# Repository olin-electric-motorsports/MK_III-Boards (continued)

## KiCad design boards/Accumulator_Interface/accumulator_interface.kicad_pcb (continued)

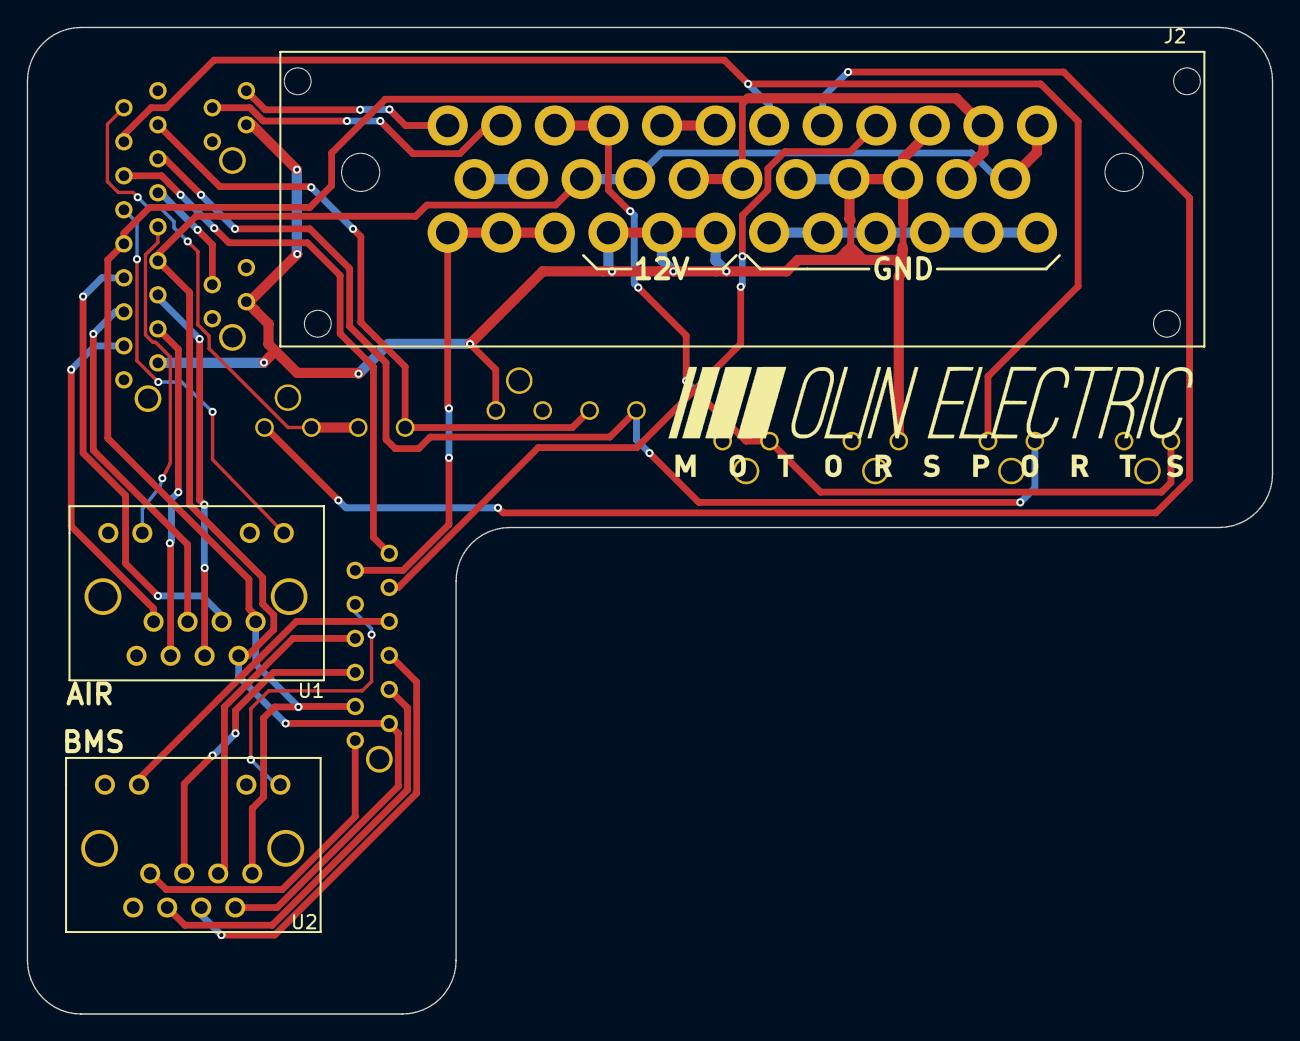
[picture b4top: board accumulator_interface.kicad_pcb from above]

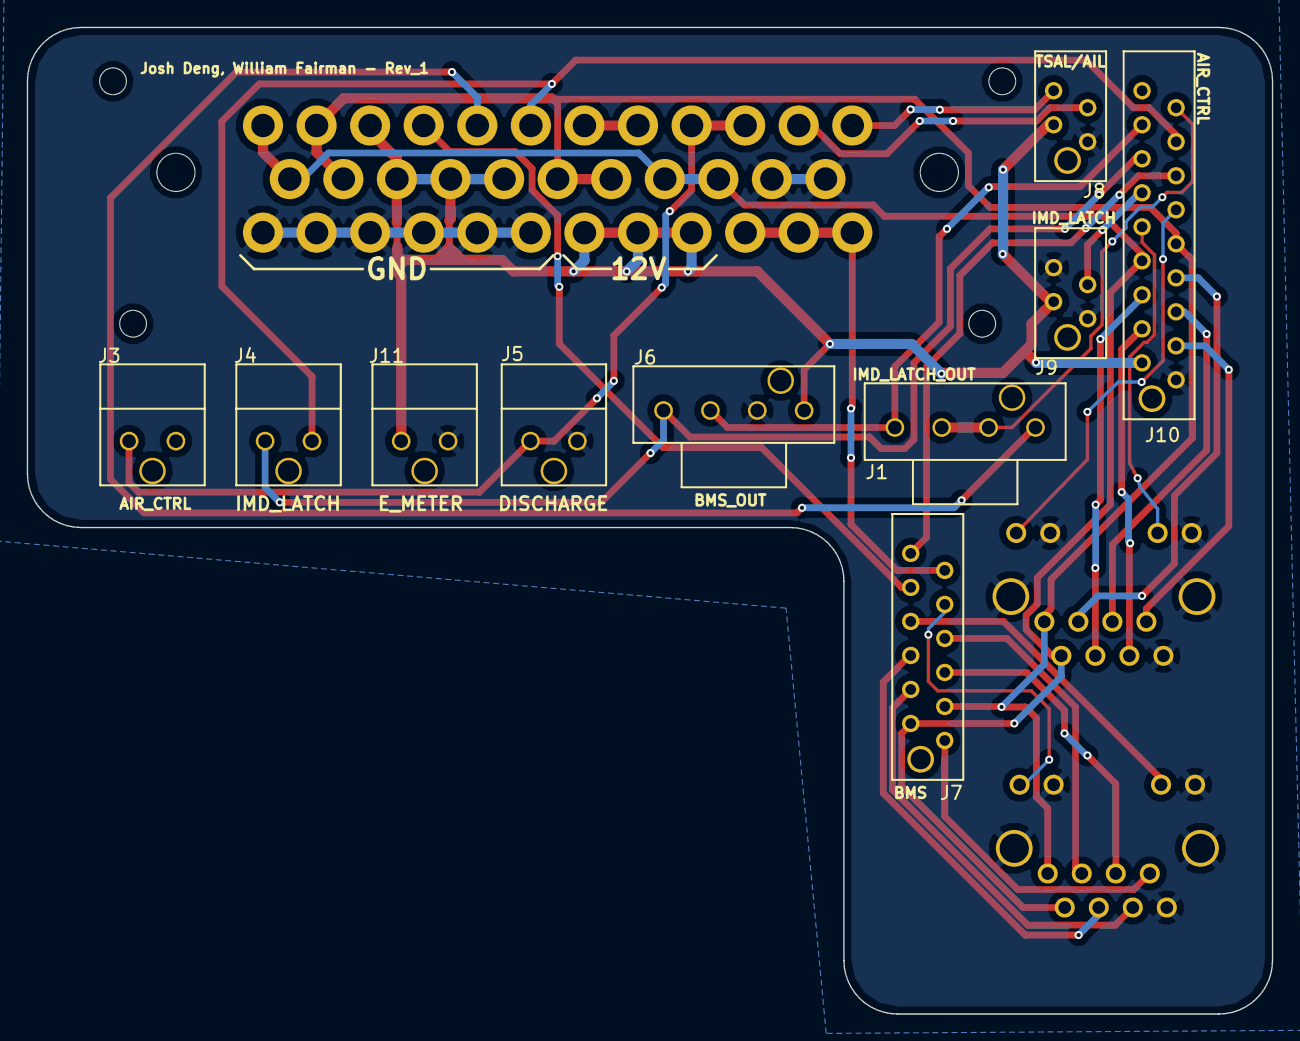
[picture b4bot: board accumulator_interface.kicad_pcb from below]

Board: 2 copper layers, 93.0 x 73.7 mm, 13 parts (10 on the bottom side), 31 nets.

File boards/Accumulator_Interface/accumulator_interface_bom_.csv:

Component,Description,Part,References,Value,Footprint,Quantity Per PCB,Datasheet,Package,MPN,MFN,PurchasingLink,PurchasingLink2,MPN2
1,ULTRAFIT CONN HDR 02CKT,Ultrafit_2,J3,AIR_CTRL,Ultrafit_2,1,,Value,WM11570-ND,Digi-Key,https://www.digikey.com/product-detail/en/molex-llc/17228611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,,
2,CONN FMALE-ON-BRD 18POS VERT T/H,micromatch_female_TOP_ENTRY_locking_18,J10,AIR_CTRL_18,micromatch_female_vert_18,1,,Value,A99500CT-ND,Digi-Key,https://www.digikey.com/product-detail/en/te-connectivity-am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,,
3,CONN FMALE-ON-BRD 12POS VERT T/H,micromatch_female_TOP_ENTRY_locking_12,J7,BMS,micromatch_female_vert_12,1,,Value,A99503CT-ND,Digi-Key,https://www.digikey.com/product-detail/en/te-connectivity-am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,,
4,Ultrafit 4 Pin Connector,Ultrafit_4,J6,BMS_Master,Ultrafit_4,1,http://www.literature.molex.com/SQLImages/kelmscott/Molex/PD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,Value,WM11574-ND,Digi-Key,https://www.digikey.com/products/en?keywords=WM11574-ND,https://www.digikey.com/product-detail/en/molex-llc/17225610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,WM11564-ND
5,ULTRAFIT CONN HDR 02CKT,Ultrafit_2,J5,DISCHARGE,Ultrafit_2,1,,Value,WM11570-ND,Digi-Key,https://www.digikey.com/product-detail/en/molex-llc/17228611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,,
6,Waterproof Panel-Mount Connector RA 35-Pin,Ampseal_35,J2,EXTERNAL,Ampseal_35,1,http://www.te.com/commerce/DocumentDelivery/DDEController?Ac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,,,,,,
7,ULTRAFIT CONN HDR 02CKT,Ultrafit_2,J11,Energy_Meter_Power,Ultrafit_2,1,,Value,WM11570-ND,Digi-Key,https://www.digikey.com/product-detail/en/molex-llc/17228611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,,
8,ULTRAFIT CONN HDR 02CKT,Ultrafit_2,J4,IMD_LATCH,Ultrafit_2,1,,Value,WM11570-ND,Digi-Key,https://www.digikey.com/product-detail/en/molex-llc/17228611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,,
9,CONN FMALE-ON-BRD 4POS VERT T/H,micromatch_female_TOP_ENTRY_locking_4,J9,IMD_LATCH,micromatch_female_vert_4,1,http://www.te.com/commerce/DocumentDelivery/DDEController?Ac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,Value,338068-4,Digi-Key,https://www.digikey.com/product-detail/en/te-connectivity-am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,,
10,Ultrafit 4 Pin Connector,Ultrafit_4,J1,INTERNAL,Ultrafit_4,1,http://www.literature.molex.com/SQLImages/kelmscott/Molex/PD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,Value,WM11574-ND,Digi-Key,https://www.digikey.com/products/en?keywords=WM11574-ND,https://www.digikey.com/product-detail/en/molex-llc/17225610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,WM11564-ND
11,CONN FMALE-ON-BRD 4POS VERT T/H,micromatch_female_TOP_ENTRY_locking_4,J8,TSAL/AIL,micromatch_female_vert_4,1,http://www.te.com/commerce/DocumentDelivery/DDEController?Ac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,Value,338068-4,Digi-Key,https://www.digikey.com/product-detail/en/te-connectivity-am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,,
12,CONN MOD JACK 8P8C VERT UNSHLD,RJ45_VT,U1,RJ45_VT_AIR,RJ45-Vertical,1,https://www.amphenolcanada.com/ProductSearch/drawings/AC/MRJ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,,,,,,
13,CONN MOD JACK 8P8C VERT UNSHLD,RJ45_VT,U2,RJ45_VT_BMS,RJ45-Vertical,1,https://www.amphenolcanada.com/ProductSearch/drawings/AC/MRJ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,,,,,,





Component Groups:,13
Component Count:,13
Fitted Components:,13
Number of PCBs:,1
Total components:,13
Schematic Version:,
Schematic Date:,
BoM Date:,Mon 26 Feb 2018 09:31:12 PM EST
Schematic Source:,/home/william/Desktop/Formula/MK_III-Boards/boards/Accumulator_Interface/accumulator_interface.sch
KiCad Version:,Eeschema 4.0.7-e2-6376~58~ubuntu16.04.1

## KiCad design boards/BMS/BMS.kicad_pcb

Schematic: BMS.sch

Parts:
C1: C_22uF; C_1206_OEM; MPN 1276-2725-1-ND
C2, C4, C5, C9, C15: C_0.1uF; C_0805_OEM; MPN 478-3352-1-ND
C3: C_100pF; C_0805_OEM; MPN 399-1122-1-ND
C6: C_47uF; C_0805_OEM; MPN 587-4280-1-ND
C7, C8: C_30pF; C_0805_OEM; MPN 1276-1130-1-ND
C14: C_10uF_16V; C_0805_OEM; MPN 1276-2399-1-ND
D1, D2, D6, D7, D8: LED_0805; LED_0805_OEM; MPN 475-1410-1-ND
D3: D_Schottky_SOD123; D_SOD-123W_OEM; MPN 1727-2394-1-ND
D4: D_Zener_18V; DO-214AA; MPN SMBJ5355B-TPMSCT-ND
F1: F_500mA_16V; Fuse_1210; MPN 507-1786-1-ND
IC1: ATMEGA16M1; TQFP-32_7x7mm_Pitch0.8mm; MPN ATMEGA16M1-AU-ND
J1, J2, J3, J5: Mounting_Hole_4-40; MPN Value
J4: Ultrafit_4; MPN WM11574-ND
J8: Ultrafit_5; UltraFit_5; MPN WM11667-ND
K1: G5Q-1A4-DC5-5V; Relay_SPST_OMRON-G5Q-1A4_OEM; MPN Z3632-ND
L1: L_4.7uH; 4.7uH_Inductor_OEM; MPN 445-6583-1-ND
P1: CONN_02X03; Pin_Header_Straight_2x03; MPN 609-3234-ND
Q1: 2N7002; SOT-23F
R1: R_1k; R_0805_OEM; MPN RNCP0805FTD1K00CT-ND
R2, R3, R9, R15, R18, R19: R_200; R_0805_OEM; MPN RMCF0805JT200RCT-ND
R4, R6, R8: R_10k; R_0805_OEM; MPN CRS0805-FX-1002ELFCT-ND
R5: R_100; R_0805_OEM; MPN RNCP0805FTD100RCT-ND
R7: R_55.1k; R_0805_OEM; MPN 311-51.1KCRCT-ND
R10: R_10k; D_0805_OEM; MPN CRS0805-FX-1002ELFCT-ND
U1: micro-match12pin; micromatch_female_ra_12
U2: CAN_Transceiver; SOIC-8_3.9x4.9mm_Pitch1.27mm_OEM; MPN MCP2561-E/SN-ND
U3: TPS561201; SOT-23-6_OEM; MPN TPS561201
U4: SN74LVC1G17; SOT-23-5_OEM
Y1: Crystal_SMD; Crystal_SMD_FA238; MPN SER3686CT-ND

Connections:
+12V: F1.1, J4.1
Acc_Fan_PWM: U1.11, U4.4 (Y)
BSPD_Current_Sense: IC1.23 ((PCINT3/AMP0-)PB3), U1.10; also elsewhere on the board
CANH: U1.2, U2.7 (CANH)
CANL: U1.3, U2.6 (CANL)
CS_iso: IC1.24 ((PCINT4/AMP0+)PB4); also elsewhere on the board
Fan_PWM: IC1.3 ((PCINT9/PSCIN1/OC1B/~SS_A~)PC1), U4.2 (A)
GND: C1.2, C2.2, C3.2, C4.2, C6.2, C7.2, C8.2, C9.2, C14.2, C15.2, D1.1 (K), D2.1 (K), D4.2 (A), IC1.5 (GND), IC1.20 (AGND), J4.2, J8.2, P1.6, Q1.2 (S), R6.2, R15.2, R18.2, R19.2, U2.2 (VSS), U2.8 (STBY), U3.1 (GND), U4.3 (GND), Y1.2, Y1.4; also elsewhere on the board
LED1: IC1.17 ((PCINT12/ADC8/ACMPN3/AMP1-)PC4), R2.1
LED2: IC1.18 ((PCINT13/ADC9/ACMP3/AMP1+)PC5), R3.1
LED3: D8.2 (A), IC1.26 ((PCINT5/ADC6/INT2/ACMPN1/AMP2-)PB5)
LED4: D7.2 (A), IC1.27 ((PCINT6/ADC7/PSCOUT1B)PB6)
LED5: D6.2 (A), IC1.30 ((PCINT8/INT3/PSCOUT1A)PC0)
MISO: IC1.1 ((PCINT18/PSCIN2/OC1A/MISO_A)PD2), P1.1, U1.5
MISO_iso: IC1.8 ((PCINT0/MISO/PSCOUT2A)PB0); also elsewhere on the board
MOSI: IC1.2 ((PCINT19/TXD/TXLIN/OC0A/~SS~/MOSI_A)PD3), P1.4, U1.4
MOSI_iso: IC1.9 ((PCINT1/MOSI/PSCOUT2B)PB1); also elsewhere on the board
unnamed: C1.1, D4.1 (K), F1.2, R1.1, R4.1, U3.3 (VIN)
unnamed: C3.1, IC1.19 (AVCC), R5.2
unnamed: C4.1, U2.3 (VDD)
unnamed: C5.1, U3.6 (VBST)
unnamed: C5.2, L1.1, U3.2 (SW)
unnamed: C7.1, IC1.11 ((PCINT26/ADC0/XTAL2)PE2), Y1.1
unnamed: C8.1, IC1.10 ((PCINT25/OC0B/XTAL1)PE1), Y1.3
unnamed: D1.2 (A), R1.2
unnamed: D2.2 (A), R9.2
unnamed: D3.2 (A), K1.5, Q1.3 (D)
unnamed: D6.1 (K), R15.1
unnamed: D7.1 (K), R18.1
unnamed: D8.1 (K), R19.1
unnamed: IC1.13 ((PCINT21/ADC2/ACMP2)PD5), J8.4
unnamed: IC1.14 ((PCINT22/ADC3/INT0/ACMPN2)PD6), J8.3
unnamed: IC1.22 ((PCINT14/ADC10/ACMP1)PC6), J8.5, R8.2
unnamed: J4.3, K1.2
unnamed: J4.4, K1.3
unnamed: R2.2, U1.8
unnamed: R3.2, U1.9
unnamed: R4.2, U3.5 (EN)
unnamed: R6.1, R7.1, U3.4 (VFB)
RESET: IC1.31 ((PCINT24/OCD/~RESET~)PE0), P1.5, R10.2, U1.7
RXCAN: IC1.7 ((PCINT11/T1/ICP1B/RXCAN)PC3), U2.4 (RXD)
SCK: IC1.12 ((PCINT20/ADC1/RXD/RXLIN/ICP1A/SCK_A)PD4), P1.3, U1.6
SCK_iso: IC1.28 ((PCINT7/ADC4/SCK/PSCOUT0B)PB7); also elsewhere on the board
Shutdown_Control: IC1.16 ((PCINT2/ADC5/INT1/ACMPN0)PB2), Q1.1 (G), U1.12
TXCAN: IC1.6 ((PCINT10/T0/TXCAN)PC2), U2.1 (TXD)
VCC: C2.1, C6.1, C9.1, C14.1, C15.1, D3.1 (K), IC1.4 (VCC), J8.1, K1.1, L1.2, P1.2, R5.1, R7.2, R8.1, R9.1, R10.1, U1.1, U4.5 (VCC); also elsewhere on the board

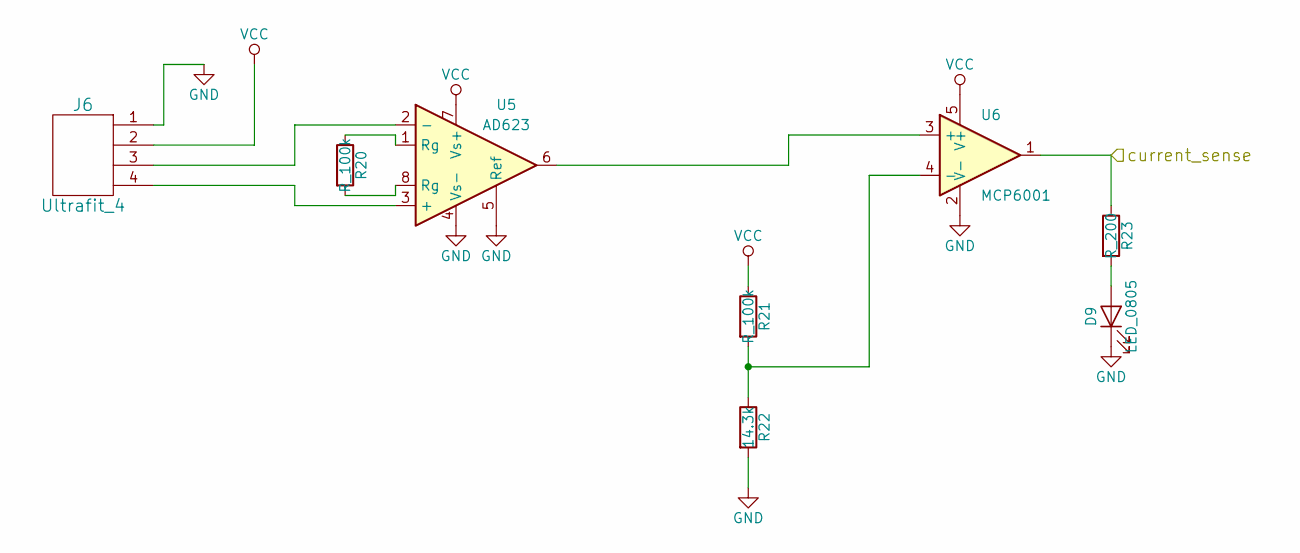
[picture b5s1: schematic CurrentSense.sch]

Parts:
D9: LED_0805; LED_0805_OEM; MPN 475-1410-1-ND
J6: Ultrafit_4; MPN WM11574-ND
R20, R21: R_100k; R_0805_OEM; MPN 311-100KCRCT-ND
R22: 14.3k; R_0805_OEM
R23: R_200; R_0805_OEM; MPN RMCF0805JT200RCT-ND
U5: AD623; AD623_SOIC-8
U6: MCP6001; SOT-23-5_OEM

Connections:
BSPD_Current_Sense: R23.1, U6.1; also elsewhere on the board
GND: D9.1 (K), J6.1, R22.2, U5.4 (Vs-), U5.5 (Ref), U6.2 (V-); also elsewhere on the board
unnamed: D9.2 (A), R23.2
unnamed: J6.3, U5.2 (-)
unnamed: J6.4, U5.3 (+)
unnamed: R20.1, U5.1 (Rg)
unnamed: R20.2, U5.8 (Rg)
unnamed: R21.2, R22.1, U6.4 (-)
unnamed: U5.6, U6.3 (+)
VCC: J6.2, R21.1, U5.7 (Vs+), U6.5 (V+); also elsewhere on the board

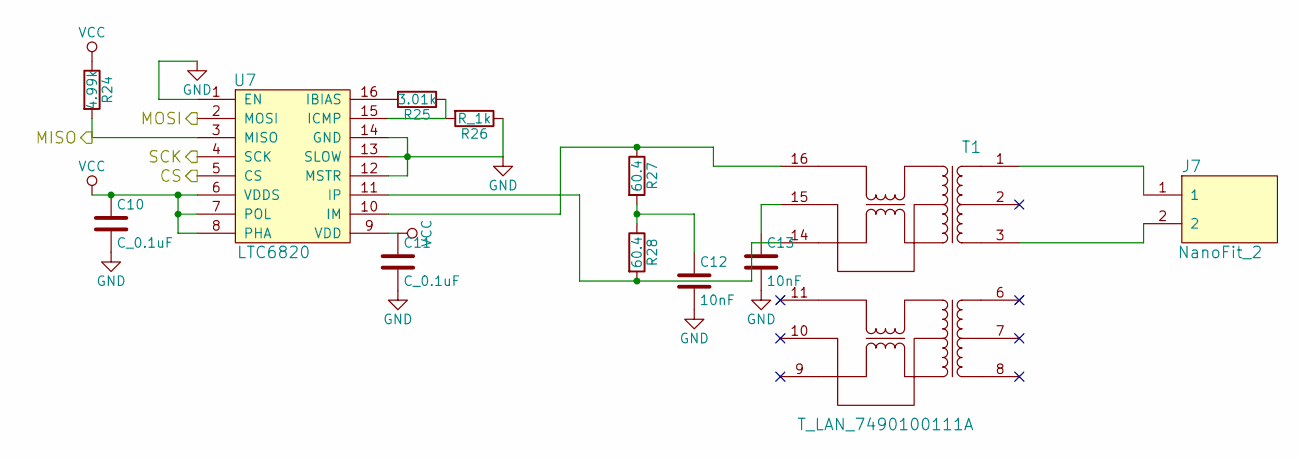
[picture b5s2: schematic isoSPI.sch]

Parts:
C10, C11: C_0.1uF; C_0805_OEM; MPN 478-3352-1-ND
C12, C13: 10nF; C_0805_OEM
J7: NanoFit_2; Molex_NanoFit_1x02x2.50mm_Angled_OEM
R24: 4.99k; R_0805_OEM
R25: 3.01k; R_0805_OEM
R26: R_1k; R_0805_OEM; MPN RNCP0805FTD1K00CT-ND
R27, R28: 60.4; R_0805_OEM
T1: T_LAN_7490100111A; 7490100111A
U7: LTC6820; LTC6820_OEM

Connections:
CS_iso: U7.5 (CS); also elsewhere on the board
GND: C10.2, C11.2, C12.2, C13.2, R26.1, U7.1 (EN), U7.12 (MSTR), U7.13 (SLOW), U7.14 (GND); also elsewhere on the board
MISO_iso: R24.2, U7.3 (MISO); also elsewhere on the board
MOSI_iso: U7.2 (MOSI); also elsewhere on the board
unnamed: C12.1, R27.2, R28.1
unnamed: C13.1, T1.15
unnamed: J7.1, T1.1
unnamed: J7.2, T1.3
unnamed: R25.1, R26.2, U7.15 (ICMP)
unnamed: R25.2, U7.16 (IBIAS)
unnamed: R27.1, T1.16, U7.10 (IM)
unnamed: R28.2, T1.14, U7.11 (IP)
SCK_iso: U7.4 (SCK); also elsewhere on the board
VCC: C10.1, C11.1, R24.1, U7.6 (VDDS), U7.7 (POL), U7.8 (PHA), U7.9 (VDD); also elsewhere on the board

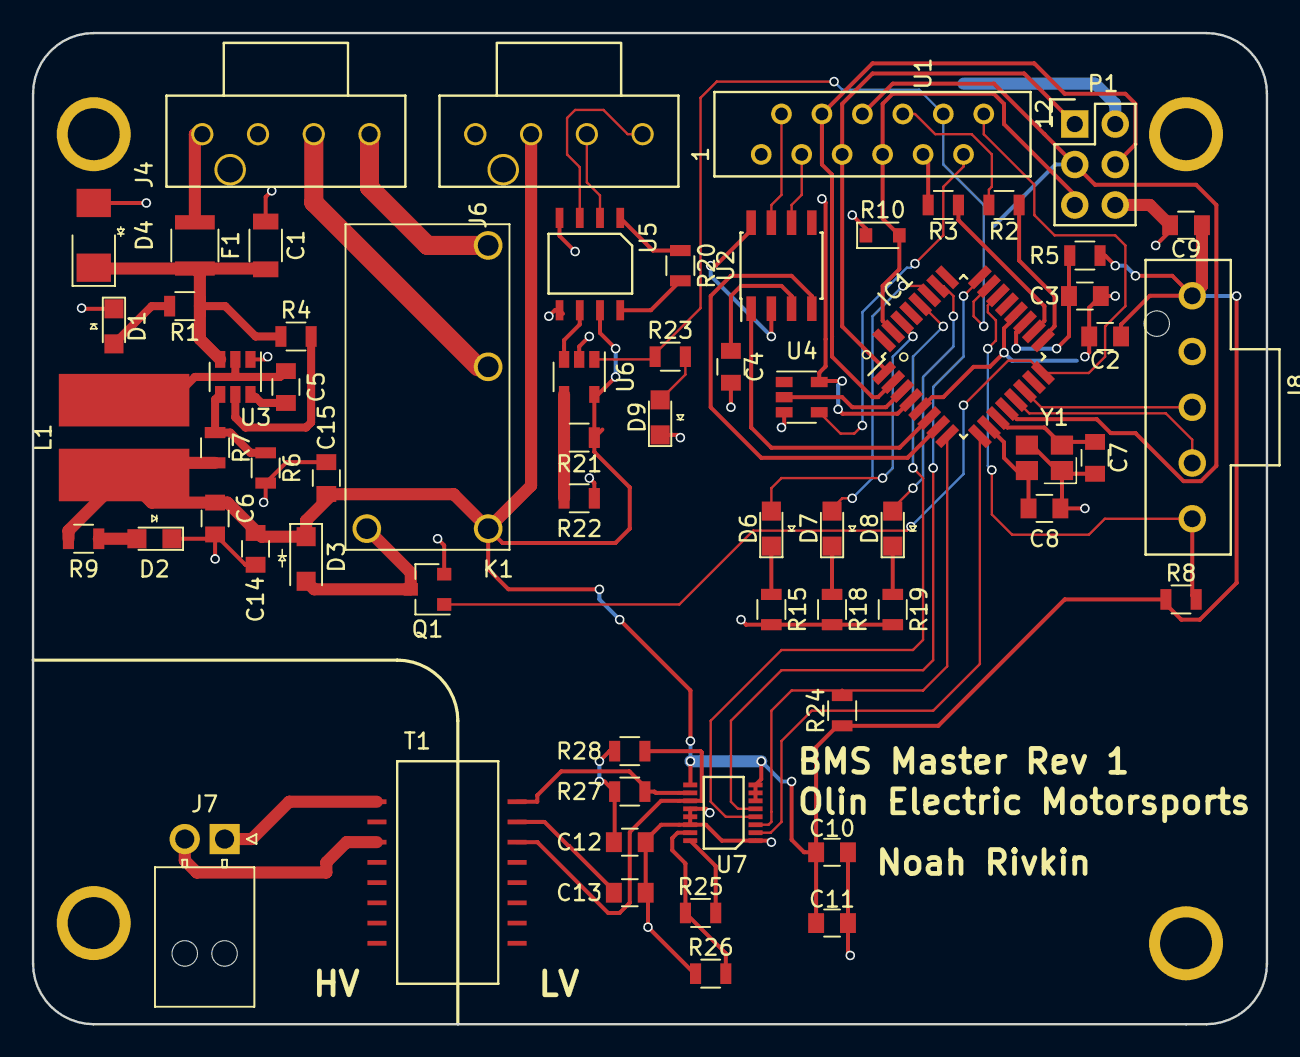
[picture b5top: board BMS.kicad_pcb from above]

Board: 2 copper layers, 77.5 x 62.2 mm, 68 parts (0 on the bottom side), 61 nets.

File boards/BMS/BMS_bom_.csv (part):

Component,Description,Part,References,Value,Footprint,Quantity Per PCB,Datasheet,Package,MPN,MFN,PurchasingLink,PurchasingLink2,MPN2
1,Unpolarized capacitor,C,C12 C13,10nF,C_0805_OEM,2,,,,,,,
2,Cap 50V 0.1uF 10% 0805,C_0.1uF,C2 C4 C5 C9 C10 C11 C15,C_0.1uF,C_0805_OEM,7,http://datasheets.avx.com/X7RDielectric.pdf,Value,478-3352-1-ND,Digi-Key,https://www.digikey.com/products/en?keywords=478-3352-1-ND,,
3,Cap 50V 100pF 5% 0805,C_100pF,C3,C_100pF,C_0805_OEM,1,https://content.kemet.com/datasheets/KEM_C1003_C0G_SMD.pdf,Value,399-1122-1-ND,Digi-Key,https://www.digikey.com/product-detail/en/kemet/C0805C101J5G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,,
4,CAP CER 10UF 16V X5R 0805,C_10uF_16V,C14,C_10uF_16V,C_0805_OEM,1,http://www.samsungsem.com/kr/support/product-search/mlcc/__i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,Value,1276-2399-1-ND,Digi-Key,https://www.digikey.com/product-detail/en/samsung-electro-me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,,
5,Unpolarized capacitor,C_22uF,C1,C_22uF,C_1206_OEM,1,http://www.samsungsem.com/kr/support/product-search/mlcc/__i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,Value,1276-2725-1-ND,Digi-Key,https://www.digikey.com/products/en?keywords=1276-2725-1-ND,,
6,Cap 50V 30pF 5% 0805,C_30pF,C7 C8,C_30pF,C_0805_OEM,2,https://media.digikey.com/pdf/Data%20Sheets/Samsung%20PDFs/C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,Value,1276-1130-1-ND,Digi-Key,https://www.digikey.com/product-detail/en/samsung-electro-me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,,
7,CAP CER 47UF 6.3V X5R 0805,C_47uF,C6,C_47uF,C_0805_OEM,1,http://www.yuden.co.jp/productdata/catalog/en/mlcc_all_e.pdf,Value,587-4280-1-ND,Digi-Key,https://www.digikey.com/product-detail/en/taiyo-yuden/JMK212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,,
8,DIODE SCHOTTKY 100V 1A SOD123,D_Schottky_SOD123,D3,D_Schottky_SOD123,D_SOD-123W_OEM,1,https://assets.nexperia.com/documents/data-sheet/PMEG10010ELR.pdf,,1727-2394-1-ND,Digi-Key,https://www.digikey.com/product-detail/en/nexperia-usa-inc/P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,,
9,DIODE ZENER 18V 5W DO214AA,D_Zener_18V,D4,D_Zener_18V,DO-214AA,1,http://www.mccsemi.com/up_pdf/SMBJ5338B-SMBJ5388B(SMB).pdf,DO-214AA (SMB),SMBJ5355B-TPMSCT-ND,Digi-Key,https://www.digikey.com/products/en?keywords=SMBJ5355B-TPMSCT-ND,,
10,LED_0805,LED_0805,D1 D2 D6 D7 D8 D9,LED_0805,LED_0805_OEM,6,http://www.osram-os.com/Graphics/XPic9/00078860_0.pdf,Value,475-1410-1-ND,Digi-Key,https://www.digikey.com/products/en?keywords=475-1410-1-ND,,
11,PTC Fuse 16V 500mA,F_500mA_16V,F1,F_500mA_16V,Fuse_1210,1,https://belfuse.com/resources/CircuitProtection/datasheets/0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,Value,507-1786-1-ND,Digi-Key,https://www.digikey.com/product-detail/en/bel-fuse-inc/0ZCH0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,,
12,"TQFP32, 16k Flash, 1k SRAM, 512B EEPROM, CAN",ATMEGA16M1,IC1,ATMEGA16M1,TQFP-32_7x7mm_Pitch0.8mm,1,http://www.atmel.com/Images/Atmel-8209-8-bit%20AVR%20ATmega1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,Value,ATMEGA16M1-AU-ND,Digi-Key,https://www.digikey.com/product-detail/en/atmel/ATMEGA16M1-A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,,
13,,NanoFit_2,J7,NanoFit_2,Molex_NanoFit_1x02x2.50mm_Angled_OEM,1,http://www.literature.molex.com/SQLImages/kelmscott/Molex/PD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,Value,WM14958-ND,Digi-Key,https://www.digikey.com/product-detail/en/molex-llc/10530712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,,
14,Ultrafit 4 Pin Connector,Ultrafit_4,J4 J6,Ultrafit_4,Ultrafit_4,2,http://www.literature.molex.com/SQLImages/kelmscott/Molex/PD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,Value,WM11574-ND,Digi-Key,https://www.digikey.com/products/en?keywords=WM11574-ND,https://www.digikey.com/product-detail/en/molex-llc/17225610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,WM11564-ND
15,,Ultrafit_5,J8,Ultrafit_5,UltraFit_5,1,http://www.literature.molex.com/SQLImages/kelmscott/Molex/PD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,Value,WM11667-ND,Digi-Key,https://www.digikey.com/product-detail/en/molex-llc/17228611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,,
16,g5q power relay,G5Q-1A4-DC5-5V,K1,G5Q-1A4-DC5-5V,Relay_SPST_OMRON-G5Q-1A4_OEM,1,http://omronfs.omron.com/en_US/ecb/products/pdf/en-g5q.pdf,,Z3632-ND,Digi-Key,https://www.digikey.com/product-detail/en/omron-electronics-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,,
17,Inductor 4.7uH 4.4A,L_4.7uH,L1,L_4.7uH,4.7uH_Inductor_OEM,1,https://product.tdk.com/info/en/documents/wdcatalog/withdraw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,Value,445-6583-1-ND,Digi-Key,https://www.digikey.com/product-detail/en/tdk-corporation/VL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,,
18,"Connector, double row, 02x03",CONN_02X03,P1,CONN_02X03,Pin_Header_Straight_2x03,1,http://portal.fciconnect.com/Comergent//fci/drawing/67996.pdf,Value,609-3234-ND,Digi-Key,https://www.digikey.com/product-detail/en/amphenol-fci/67997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,,
19,"50V Vds, 0.22 A Id, N-channel MOSFET, SOT-23",2N7002,Q1,2N7002,SOT-23F,1,https://www.fairchildsemi.com/datasheets/BS/BSS138.pdf,,,,,,
20,Resistor,R,R22,14.3k,R_0805_OEM,1,,,,,,,
21,Resistor,R,R25,3.01k,R_0805_OEM,1,,,,,,,
22,Resistor,R,R24,4.99k,R_0805_OEM,1,https://industrial.panasonic.com/cdbs/www-data/pdf/RDM0000/A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,Value,P4.99KDACT-ND,Digi-Key,https://www.digikey.com/product-detail/en/panasonic-electron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,,
23,Resistor,R,R27 R28,60.4,R_0805_OEM,2,https://industrial.panasonic.com/cdbs/www-data/pdf/RDA0000/A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,Value,P60.4CCT-ND,Digi-Key,https://www.digikey.com/product-detail/en/panasonic-electron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,,
24,Res 100 1%,R_100,R5,R_100,R_0805_OEM,1,https://www.seielect.com/Catalog/SEI-rncp.pdf,Value,RNCP0805FTD100RCT-ND,Digi-Key,https://www.digikey.com/products/en?keywords=RNCP0805FTD100RCT-ND,,
25,Res 100k 1%,R_100k,R20 R21,R_100k,R_0805_OEM,2,http://www.yageo.com.tw/exep/pages/download/literatures/PYu-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,Value,311-100KCRCT-ND,Digi-Key,https://www.digikey.com/products/en?keywords=311-100KCRCT-ND,,
26,Res 10k 1%,R_10k,R10,R_10k,D_0805_OEM,1,http://www.bourns.com/data/global/pdfs/CRS.pdf,Value,CRS0805-FX-1002ELFCT-ND,Digi-Key,https://www.digikey.com/products/en?keywords=CRS0805-FX-1002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,,
27,Res 10k 1%,R_10k,R4 R6 R8,R_10k,R_0805_OEM,3,http://www.bourns.com/data/global/pdfs/CRS.pdf,Value,CRS0805-FX-1002ELFCT-ND,Digi-Key,https://www.digikey.com/products/en?keywords=CRS0805-FX-1002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,,
28,Res 1k 1%,R_1k,R1 R26,R_1k,R_0805_OEM,2,https://www.seielect.com/Catalog/SEI-rncp.pdf,Value,RNCP0805FTD1K00CT-ND,Digi-Key,https://www.digikey.com/products/en?keywords=RNCP0805FTD1K00CT-ND,,
29,Res 200 5%,R_200,R2 R3 R9 R15 R18 R19 R23,R_200,R_0805_OEM,7,https://www.seielect.com/Catalog/SEI-RMCF_RMCP.pdf,Value,RMCF0805JT200RCT-ND,Digi-Key,https://www.digikey.com/products/en?keywords=RMCF0805JT200RCT-ND,,
30,Res 55.1k 1%,R_55.1k,R7,R_55.1k,R_0805_OEM,1,http://www.yageo.com.tw/exep/pages/download/literatures/PYu-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,Value,311-51.1KCRCT-ND,Digi-Key,https://www.digikey.com/products/en?keywords=311-51.1KCRCT-ND,,
31,,T_LAN_7490100111A,T1,T_LAN_7490100111A,7490100111A,1,http://katalog.we-online.de/pbs/datasheet/7490100111A.pdf,Value,732-5711-1-ND,Digi-Key,https://www.digikey.com/product-detail/en/wurth-electronics-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,,
32,"Low Cost, Low Power, Instrumentation Amplifier, DIP-8/SOIC-8",AD623,U5,AD623,AD623_SOIC-8,1,http://www.analog.com/media/en/technical-documentation/data-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,,,,,,
33,"High-Speed CAN Transceiver, 1Mbps, 5V supply, SPLIT pin, -40C to +125C, SOIC8 package",CAN_Transceiver,U2,CAN_Transceiver,SOIC-8_3.9x4.9mm_Pitch1.27mm_OEM,1,http://www.microchip.com/mymicrochip/filehandler.aspx?ddocna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,Value,MCP2561-E/SN-ND,Digi-Key,https://www.digikey.com/products/en?keywords=mcp2561-e%2Fsn,,
34,,LTC6820,U7,LTC6820,LTC6820_OEM,1,,,,,,,
35,"10 MHz, 850 µA Op Amps, SOT-23-5",MCP6001,U6,MCP6001,SOT-23-5_OEM,1,http://ww1.microchip.com/downloads/en/DeviceDoc/22141b.pdf,,,,,,
36,Single Schmitt-Trigger Buffer,SN74LVC1G17,U4,SN74LVC1G17,SOT-23-5_OEM,1,,,,,,,
37,4.5V - 17V Input 1A Synchronous Buck Converter,TPS561201,U3,TPS561201,SOT-23-6_OEM,1,http://www.ti.com/lit/ds/symlink/tps561201.pdf,Value,TPS561201,Digi-Key,https://www.digikey.com/products/en?keywords=296-46928-1-ND,,
38,,micro-match12pin,U1,micro-match12pin,micromatch_female_ra_12,1,,,,,,,
39,"Two pin crystal, two ground/package pins (pin2 and 3) small symbol",Crystal_SMD,Y1,Crystal_SMD,Crystal_SMD_FA238,1,https://support.epson.biz/td/api/doc_check.php?dl=brief_FA-2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,Value,SER3686CT-ND,Digi-Key,https://www.digikey.com/products/en?keywords=SER3686CT-ND,,
,,,,,,,,,,,,,
,,,,,,,,,,,,,
,,,,,,,,,,,,,
,,,,,,,,,,,,,
,,,,,,,,,,,,,
Component Groups:,39,,,,,,,,,,,,
Component Count:,64,,,,,,,,,,,,
Fitted Components:,64,,,,,,,,,,,,
Number of PCBs:,1,,,,,,,,,,,,
Total components:,64,,,,,,,,,,,,
Schematic Version:,,,,,,,,,,,,,
Schematic Date:,,,,,,,,,,,,,
BoM Date:,Thu 22 Feb 2018 12:18:33 PM EST,,,,,,,,,,,,
Schematic Source:,/home/noah/formula/MK_III-Boards/boards/BMS/BMS.sch,,,,,,,,,,,,
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
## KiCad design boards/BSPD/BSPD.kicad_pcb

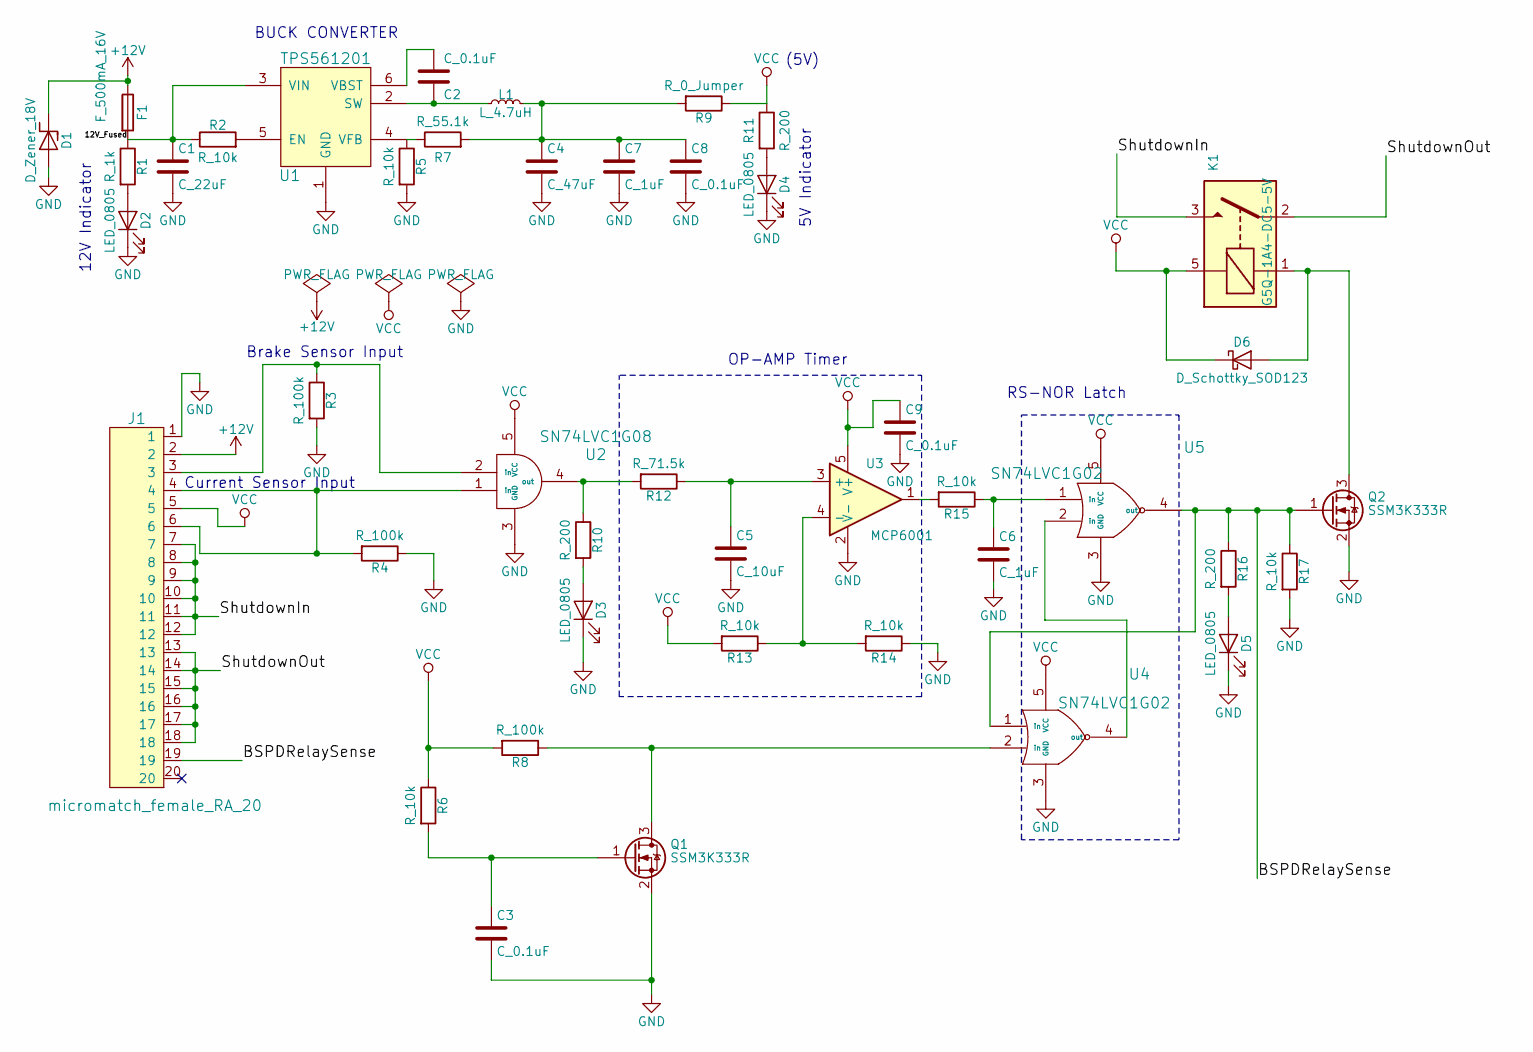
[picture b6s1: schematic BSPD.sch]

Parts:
C1: C_22uF; C_1206_OEM; MPN 1276-2725-1-ND
C2, C3, C8, C9: C_0.1uF; C_0805_OEM; MPN 478-3352-1-ND
C4: C_47uF; C_0805_OEM; MPN 587-4280-1-ND
C5: C_10uF; C_0805_OEM; MPN 478-5167-1-ND
C6, C7: C_1uF; C_0805_OEM; MPN 478-10487-1-ND
D1: D_Zener_18V; DO-214AA; MPN SMBJ5355B-TPMSCT-ND
D2, D3, D4, D5: LED_0805; LED_0805_OEM; MPN 475-1410-1-ND
D6: D_Schottky_SOD123; D_SOD-123W_OEM; MPN 1727-2394-1-ND
F1: F_500mA_16V; Fuse_1210; MPN 507-1786-1-ND
J1: micromatch_female_RA_20; micromatch_female_ra_20; MPN A99490CT-ND
K1: G5Q-1A4-DC5-5V; Relay_SPST_OMRON-G5Q-1A4_OEM; MPN Z3632-ND
L1: L_4.7uH; 4.7uH_Inductor_OEM; MPN 445-6583-1-ND
Q1, Q2: SSM3K333R; SOT-23F; MPN SSM3K333RLFCT-ND
R1: R_1k; R_0805_OEM; MPN RNCP0805FTD1K00CT-ND
R2, R5, R6, R13, R14, R15, R17: R_10k; R_0805_OEM; MPN CRS0805-FX-1002ELFCT-ND
R3, R4, R8: R_100k; R_0805_OEM; MPN 311-100KCRCT-ND
R7: R_55.1k; R_0805_OEM; MPN 311-51.1KCRCT-ND
R9: R_0_Jumper; R_2512_OEM; MPN A121322CT-ND
R10, R11, R16: R_200; R_0805_OEM; MPN RMCF0805JT200RCT-ND
R12: R_71.5k; R_0805_OEM; MPN RC0805FR-0771K5L
U1: TPS561201; SOT-23-6_OEM; MPN TPS561201
U2: SN74LVC1G08; SOT-23-5_OEM; MPN SN74LVC1G08DBVR
U3: MCP6001; SOT-23-5_OEM; MPN MCP6001T-I/OT
U4, U5: SN74LVC1G02; SOT-23-5_OEM; MPN SN74LVC1G02DBVR

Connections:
+12V: D1.1 (K), F1.1, J1.2
/12V_Fused: C1.1, F1.2, R1.1, R2.1, U1.3 (VIN)
/BSPDRelaySense: J1.19, Q2.1 (G), R16.1, R17.1, U4.1 (in), U5.4 (out)
/ShutdownIn: J1.7, J1.8, J1.9, J1.10, J1.11, J1.12, K1.3
/ShutdownOut: J1.13, J1.14, J1.15, J1.16, J1.17, J1.18, K1.2
GND: C1.2, C3.2, C4.2, C5.2, C6.2, C7.2, C8.2, C9.2, D1.2 (A), D2.1 (K), D3.1 (K), D4.1 (K), D5.1 (K), J1.1, Q1.2 (S), Q2.2 (S), R3.2, R4.1, R5.2, R14.1, R17.2, U1.1 (GND), U2.3 (GND), U3.2 (V-), U4.3 (GND), U5.3 (GND)
unnamed: C2.1, U1.6 (VBST)
unnamed: C2.2, L1.1, U1.2 (SW)
unnamed: C3.1, Q1.1 (G), R6.2
unnamed: C4.1, C7.1, C8.1, L1.2, R7.2, R9.2
unnamed: C5.1, R12.1, U3.3 (+)
unnamed: C6.1, R15.1, U5.1 (in)
unnamed: D2.2 (A), R1.2
unnamed: D3.2 (A), R10.2
unnamed: D4.2 (A), R11.2
unnamed: D5.2 (A), R16.2
unnamed: D6.2 (A), K1.1, Q2.3 (D)
unnamed: J1.3, R3.1, U2.2 (in)
unnamed: J1.4, J1.6, R4.2, U2.1 (in)
unnamed: Q1.3 (D), R8.1, U4.2 (in)
unnamed: R2.2, U1.5 (EN)
unnamed: R5.1, R7.1, U1.4 (VFB)
unnamed: R10.1, R12.2, U2.4 (out)
unnamed: R13.1, R14.2, U3.4 (-)
unnamed: R15.2, U3.1
unnamed: U4.4 (out), U5.2 (in)
VCC: C9.1, D6.1 (K), J1.5, K1.5, R6.1, R8.2, R9.1, R11.1, R13.2, U2.5 (VCC), U3.5 (V+), U4.5 (VCC), U5.5 (VCC)

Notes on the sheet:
BUCK CONVERTER
12V Indicator
5V Indicator
(5V)
Brake Sensor Input
Current Sensor Input
OP-AMP Timer
RS-NOR Latch
